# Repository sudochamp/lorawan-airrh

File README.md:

> [!IMPORTANT]
> This project is a work in progress. The board is routed and passes DRC but has not been fabricated or tested yet.

# LoRaWAN AirRH

A slim, battery-powered LoRaWAN sensor node for monitoring temperature and humidity in warehouses, cold storage, greenhouses and FMCG storage. Readings are shown on an e-ink display, logged to onboard flash and sent to a LoRaWAN gateway. It runs on two AAA cells and needs no app, Wi-Fi or cloud account.

This repository holds **SKU A (Environmental)**. A mains-powered air-quality variant (SKU B) is planned as a separate board. See [PLAN.md](PLAN.md).

*Top: RAK811 LoRa module, nPM2100 PMIC, sensors, e-ink FPC connector and display booster.*

*Bottom: 2×AAA holder, Tag-Connect SWD pads, and the thermally isolated SHT45 island (top right in the top view).*

## Features

| | |
|---|---|
| **Radio** | LoRaWAN (OTAA) via RAK811 module (STM32L1 + SX1276), EU868, U.FL antenna connector |
| **Temperature / humidity** | Sensirion SHT45 on a slotted, copper-free island to keep board heat off the sensor |
| **Light** | TI OPT3004, 23-bit ambient light with threshold interrupt (door-open / light-exposure logging) |
| **Motion** | ST LIS2DW12, ultra-low-power accelerometer for shock and tilt detection |
| **Display** | 2.13" GDEY0213B74 e-ink panel. It is bistable, so it keeps showing the last reading with no power |
| **Logging** | Winbond W25Q16JV, 16 Mbit SPI flash |
| **Power** | 2×AAA alkaline into a Nordic nPM2100 boost PMIC (0.7–3.4 V input), with a ship/wake button |
| **Debug** | Tag-Connect TC2030 SWD (no header), UART test points |
| **Enclosure target** | IP54 |
| **Operating range** | 0 to +50 °C. The limit comes from the e-ink panel; all other parts are rated to −40 °C |

## Hardware

| Ref | Part | Function |
|---|---|---|
| U2 | RAK811-HF-EU868 | LoRaWAN module and application MCU |
| U3 | nPM2100-QEAA | Boost PMIC, battery fuel gauge, ship mode |
| U1 | SHT45-AD1B | Temperature and humidity |
| U6 | OPT3004DTSR | Ambient light |
| U5 | LIS2DW12TR | Accelerometer |
| U4 | W25Q16JVSS | Data-logging flash |
| J2 | Hirose FH12-24S-0.5SH | 24-pin FPC connector for the e-ink panel |
| J4 | Hirose U.FL-R-SMT-1 | Antenna connector |
| BT1 | Keystone 2468 | 2×AAA battery holder |
| J3 | Tag-Connect TC2030-IDC-NL | SWD programming |

**Buses**
- **I2C1**: SHT45 (0x44), OPT3004 (0x45), LIS2DW12 (0x19), nPM2100, with 4.7 k pull-ups.
- **SPI**: bit-banged SCK/MOSI shared between the display and flash, with separate chip selects. The RAK811 has no free hardware SPI.

## PCB

- 36 × 75.2 mm, 4 layers, 1.6 mm, ENIG, built to JLCPCB standard 4-layer rules (JLC04161H-7628).
- Stackup is signal / GND / GND / signal. Power is routed as traces, and both inner layers are solid ground.
- 50 Ω grounded coplanar waveguide from the RAK811 to the U.FL: 0.371 mm track with a 0.2 mm gap over In1 GND, fenced with ground vias. A pi-match footprint is included (fitted as 0 Ω, capacitors not populated).
- Hexagonal GND stitching-via grid across the board.
- Custom design rules are in [`lorawan-airrh.kicad_dru`](lorawan-airrh/lorawan-airrh.kicad_dru): JLC via and drill limits, the RF track, and clearance for the ±20 V display rails.

## Firmware notes

The board depends on firmware for these:

1. **Raise the supply before the first LoRa transmission.** VSET is left open, so the nPM2100 starts at 3.0 V. The RAK811 needs 3.15–3.45 V, so write `BOOST.VOUT` = 3.3 V over I2C first.
2. **Enable the MCU's internal pull-up on `LIGHT_INT`.** The OPT3004 interrupt output is open-drain and has no external pull-up.
3. **Skip display refreshes below 0 °C** (use the SHT45 reading). The panel is only rated to refresh from 0 to +50 °C, and the last image stays visible anyway.
4. Keep the LIS2DW12 CS and SA0 pins high. They are tied high on the board; driving either low draws about 160 µA through the internal pull-ups.

## Repository layout

```
lorawan-airrh/          KiCad 10 project (schematic, PCB, local symbols/footprints/3D models)
Datasheets/             Datasheets for the main parts
images/                 Board renders
Abstract.md             Product concept and market notes
Design Requirements.md  Requirements for this model
PLAN.md                 Engineering plan, design decisions and status log
```

## Status

- [x] Schematic, ERC clean
- [x] Placement and routing, DRC clean, no schematic mismatches
- [ ] BOM with MPN / LCSC part numbers
- [ ] Confirm the e-ink FPC contact side against a panel sample
- [ ] Fabrication outputs (Gerbers, drill, pick-and-place)
- [ ] Bring-up and firmware

## License

[GPL-3.0](LICENSE)

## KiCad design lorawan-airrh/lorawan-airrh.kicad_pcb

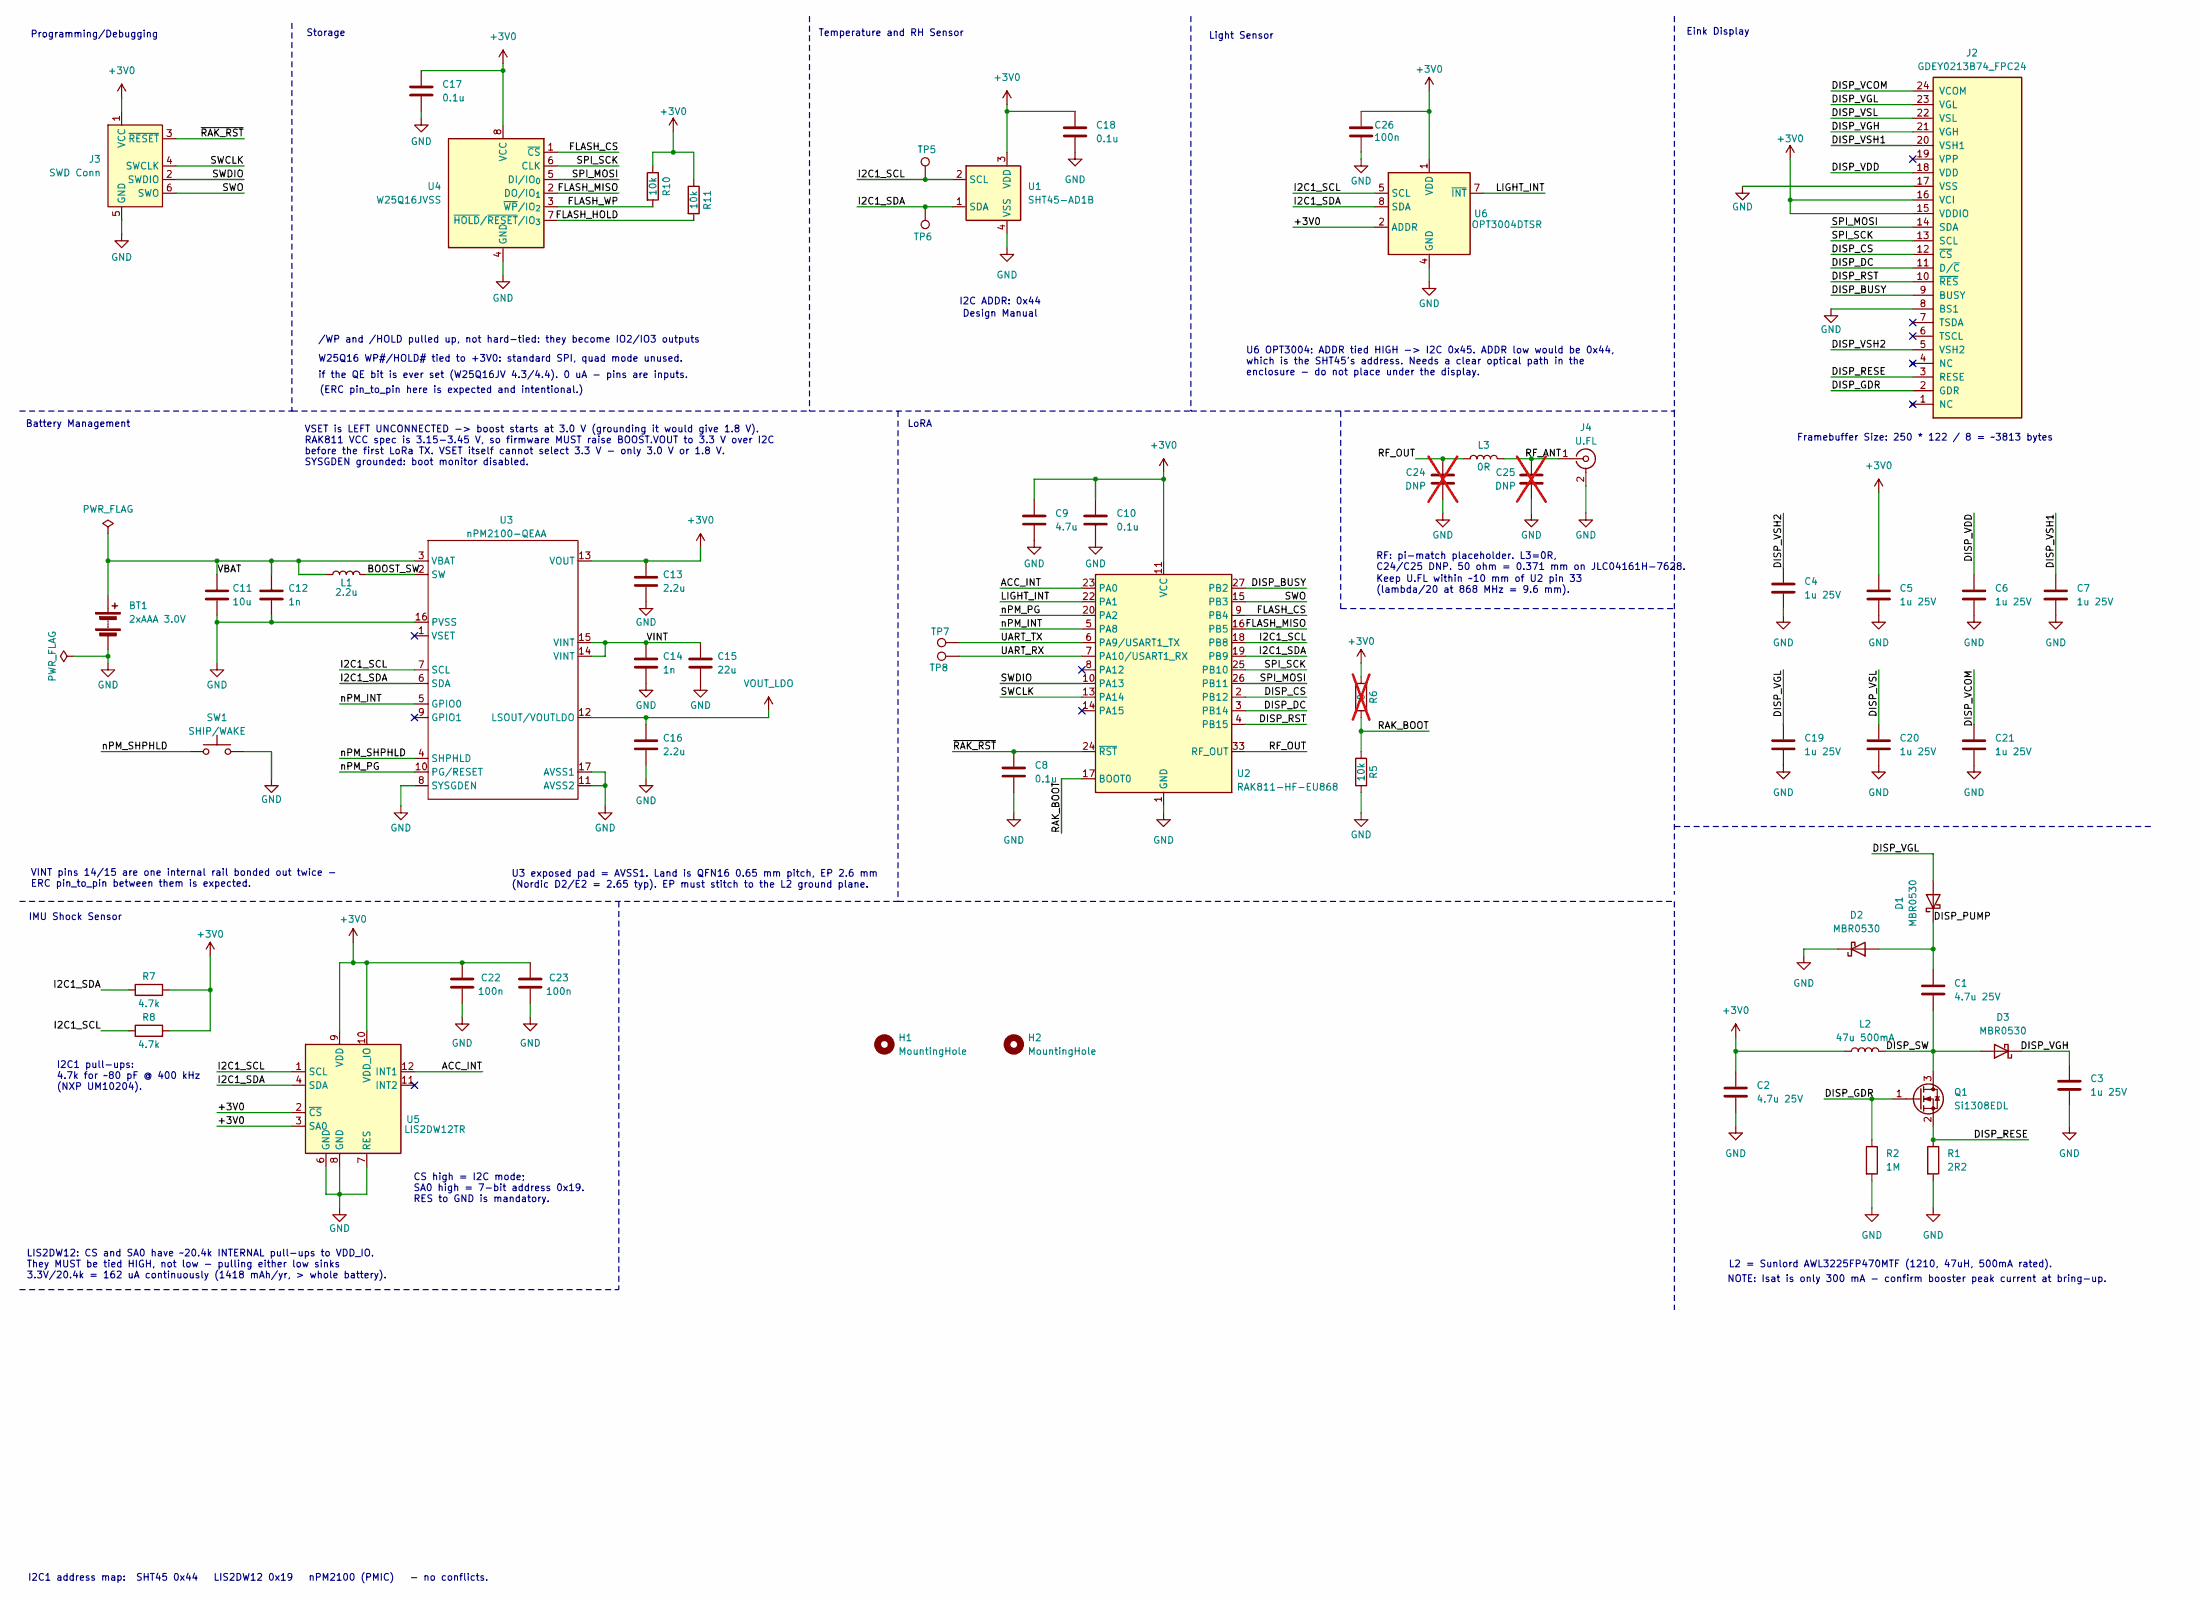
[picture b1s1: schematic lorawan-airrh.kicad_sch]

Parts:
BT1: 2xAAA 3.0V; BatteryHolder_Keystone_2468_2xAAA
C1, C2: 4.7u 25V; C_0805_2012Metric
C3, C4, C5, C6, C7, C19, C20, C21: 1u 25V; C_0603_1608Metric
C8, C10, C17, C18: 0.1u; C_0402_1005Metric
C9: 4.7u; C_0402_1005Metric
C11: 10u; C_0402_1005Metric
C12, C14: 1n; C_0402_1005Metric
C13, C16: 2.2u; C_0402_1005Metric
C15: 22u; C_0402_1005Metric
C22, C23, C26: 100n; C_0402_1005Metric
C24, C25: DNP; C_0402_1005Metric; not fitted
D1, D2, D3: MBR0530; D_SOD-123
H1, H2: MountingHole; MountingHole_2.2mm_M2
J2: GDEY0213B74_FPC24; Hirose_FH12-24S-0.5SH_1x24-1MP_P0.50mm_Horizontal; MPN FH12-24S-0.5SH(55); LCSC C202112
J3: SWD Conn; Tag-Connect_TC2030-IDC-NL_2x03_P1.27mm_Vertical
J4: U.FL; U.FL_Hirose_U.FL-R-SMT-1_Vertical
L1: 2.2u; L_0603_1608Metric
L2: 47u 500mA; L_1210_3225Metric
L3: 0R; L_0402_1005Metric
Q1: Si1308EDL; SOT-323_SC-70
R1: 2R2; R_0603_1608Metric
R2: 1M; R_0402_1005Metric
R5, R10, R11: 10k; R_0402_1005Metric
R6: 0; R_0402_1005Metric; not fitted
R7, R8: 4.7k; R_0402_1005Metric
SW1: SHIP/WAKE; SW_Push_1P1T_XKB_TS-1187A
TP5, TP6, TP7, TP8: TestPoint; TestPoint_Pad_D1.5mm
U1: SHT45-AD1B; Sensirion_DFN-4_1.5x1.5mm_P0.8mm_SHT4x_NoCentralPad
U2: RAK811-HF-EU868; RAK811
U3: nPM2100-QEAA; UQFN-16-1EP_4x4mm_P0.65mm_EP2.6x2.6mm_ThermalVias
U4: W25Q16JVSS; SOIC-8_5.3x5.3mm_P1.27mm
U5: LIS2DW12TR; LGA-12_2x2mm_P0.5mm
U6: OPT3004DTSR; Texas_DTS0008A_SOT-5X3-8_2.1x1.9mm_P0.5mm

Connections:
+3V0: C2.1, C5.1, C9.1, C10.1, C13.1, C17.1, C18.1, C22.1, C23.1, C26.1, J2.15 (VDDIO), J2.16 (VCI), J3.1 (VCC), L2.1, R6.1, R7.2, R8.2, R10.1, R11.1, U1.3 (VDD), U2.11 (VCC), U3.13 (VOUT), U4.8 (VCC), U5.2 (~CS), U5.3 (SA0), U5.9 (VDD), U5.10 (VDD_IO), U6.1 (VDD), U6.2 (ADDR)
/ACC_INT: U2.23 (PA0), U5.12 (INT1)
/BOOST_SW: L1.2, U3.2 (SW)
/DISP_BUSY: J2.9 (BUSY), U2.27 (PB2)
/DISP_CS: J2.12 (~CS), U2.2 (PB12)
/DISP_DC: J2.11 (D/~C), U2.3 (PB14)
/DISP_GDR: J2.2 (GDR), Q1.1 (G), R2.1
/DISP_PUMP: C1.1, D1.1 (K), D2.2 (A)
/DISP_RESE: J2.3 (RESE), Q1.2 (S), R1.1
/DISP_RST: J2.10 (~RES), U2.4 (PB15)
/DISP_SW: C1.2, D3.2 (A), L2.2, Q1.3 (D)
/DISP_VCOM: C21.1, J2.24 (VCOM)
/DISP_VDD: C6.1, J2.18 (VDD)
/DISP_VGH: C3.1, D3.1 (K), J2.21 (VGH)
/DISP_VGL: C19.1, D1.2 (A), J2.23 (VGL)
/DISP_VSH1: C7.1, J2.20 (VSH1)
/DISP_VSH2: C4.1, J2.5 (VSH2)
/DISP_VSL: C20.1, J2.22 (VSL)
/FLASH_CS: U2.9 (PB4), U4.1 (~CS)
/FLASH_HOLD: R11.2, U4.7 (~HOLD/~RESET/IO_{3})
/FLASH_MISO: U2.16 (PB5), U4.2 (DO/IO_{1})
/FLASH_WP: R10.2, U4.3 (~WP/IO_{2})
/I2C1_SCL: R8.1, TP5.1 (1_1), U1.2 (SCL), U2.18 (PB8), U3.7 (SCL), U5.1 (SCL), U6.5 (SCL)
/I2C1_SDA: R7.1, TP6.1 (1_1), U1.1 (SDA), U2.19 (PB9), U3.6 (SDA), U5.4 (SDA), U6.8 (SDA)
/LIGHT_INT: U2.22 (PA1), U6.7 (~INT)
/RAK_BOOT: R5.1, R6.2, U2.17 (BOOT0)
/RF_ANT: C25.1, J4.1 (In), L3.2
/RF_OUT: C24.1, L3.1, U2.33 (RF_OUT)
/SPI_MOSI: J2.14 (SDA), U2.26 (PB11), U4.5 (DI/IO_{0})
/SPI_SCK: J2.13 (SCL), U2.25 (PB10), U4.6 (CLK)
/SWCLK: J3.4 (SWCLK), U2.13 (PA14)
/SWDIO: J3.2 (SWDIO), U2.10 (PA13)
/SWO: J3.6 (SWO), U2.15 (PB3)
/UART_RX: TP8.1 (1_1), U2.7 (PA10/USART1_RX)
/UART_TX: TP7.1 (1_1), U2.6 (PA9/USART1_TX)
/VBAT: BT1.1 (+), C11.1, C12.1, L1.1, U3.3 (VBAT)
/VINT: C14.1, C15.1, U3.14 (VINT), U3.15 (VINT)
/nPM_INT: U2.5 (PA8), U3.5 (GPIO0)
/nPM_PG: U2.20 (PA2), U3.10 (PG/RESET)
/nPM_SHPHLD: SW1.1, U3.4 (SHPHLD)
/~RAK_RST: C8.1, J3.3 (~RESET), U2.24 (~RST)
GND: BT1.2 (-), C2.2, C3.2, C4.2, C5.2, C6.2, C7.2, C8.2, C9.2, C10.2, C11.2, C12.2, C13.2, C14.2, C15.2, C16.2, C17.2, C18.2, C19.2, C20.2, C21.2, C22.2, C23.2, C24.2, C25.2, C26.2, D2.1 (K), J2.8 (BS1), J2.17 (VSS), J3.5 (GND), J4.2 (Ext), R1.2, R2.2, R5.2, SW1.2, U1.4 (VSS), U2.1 (GND), U2.12 (GND), U2.21 (GND), U2.28 (GND), U2.29 (GND), U2.30 (GND), U2.31 (GND), U2.32 (GND), U2.34 (GND), U3.8 (SYSGDEN), U3.11 (AVSS2), U3.16 (PVSS), U3.17 (AVSS1), U4.4 (GND), U5.6 (GND), U5.7 (RES), U5.8 (GND), U6.4 (GND)
VOUT_LDO: C16.1, U3.12 (LSOUT/VOUTLDO)

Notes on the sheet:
U3 exposed pad = AVSS1. Land is QFN16 0.65 mm pitch, EP 2.6 mm (Nordic D2/E2 = 2.65 typ). EP must stitch to the L2 ground plane.
Keep U.FL within ~10 mm of U2 pin 33 (lambda/20 at 868 MHz = 9.6 mm).
I2C1 pull-ups: 4.7k for ~80 pF @ 400 kHz (NXP UM10204).
Design Manual
Battery Management
VINT pins 14/15 are one internal rail bonded out twice - ERC pin_to_pin between them is expected.
RF: pi-match placeholder. L3=0R, C24/C25 DNP. 50 ohm = 0.371 mm on JLC04161H-7628.
Eink Display
/WP and /HOLD pulled up, not hard-tied: they become IO2/IO3 outputs
IMU Shock Sensor
Programming/Debugging
(ERC pin_to_pin here is expected and intentional.)
I2C1 address map: SHT45 0x44 LIS2DW12 0x19 nPM2100 (PMIC) - no conflicts.
CS high = I2C mode; SA0 high = 7-bit address 0x19. RES to GND is mandatory.
if the QE bit is ever set (W25Q16JV 4.3/4.4). 0 uA - pins are inputs.
Temperature and RH Sensor
LoRA
L2 = Sunlord AWL3225FP470MTF (1210, 47uH, 500mA rated).
Light Sensor
VSET is LEFT UNCONNECTED -> boost starts at 3.0 V (grounding it would give 1.8 V). RAK811 VCC spec is 3.15-3.45 V, so firmware MUST raise BOOST.VOUT to 3.3 V over I2C before the first LoRa TX. VSET itself cannot select 3.3 V - only 3.0 V or 1.8 V. SYSGDEN grounded: boot monitor disabled.
NOTE: Isat is only 300 mA - confirm booster peak current at bring-up.
I2C ADDR: 0x44
U6 OPT3004: ADDR tied HIGH -> I2C 0x45. ADDR low would be 0x44, which is the SHT45's address. Needs a clear optical path in the enclosure - do not place under the display.
Framebuffer Size: 250 * 122 / 8 = ~3813 bytes
Storage
W25Q16 WP#/HOLD# tied to +3V0: standard SPI, quad mode unused.
LIS2DW12: CS and SA0 have ~20.4k INTERNAL pull-ups to VDD_IO. They MUST be tied HIGH, not low - pulling either low sinks 3.3V/20.4k = 162 uA continuously (1418 mAh/yr, > whole battery).

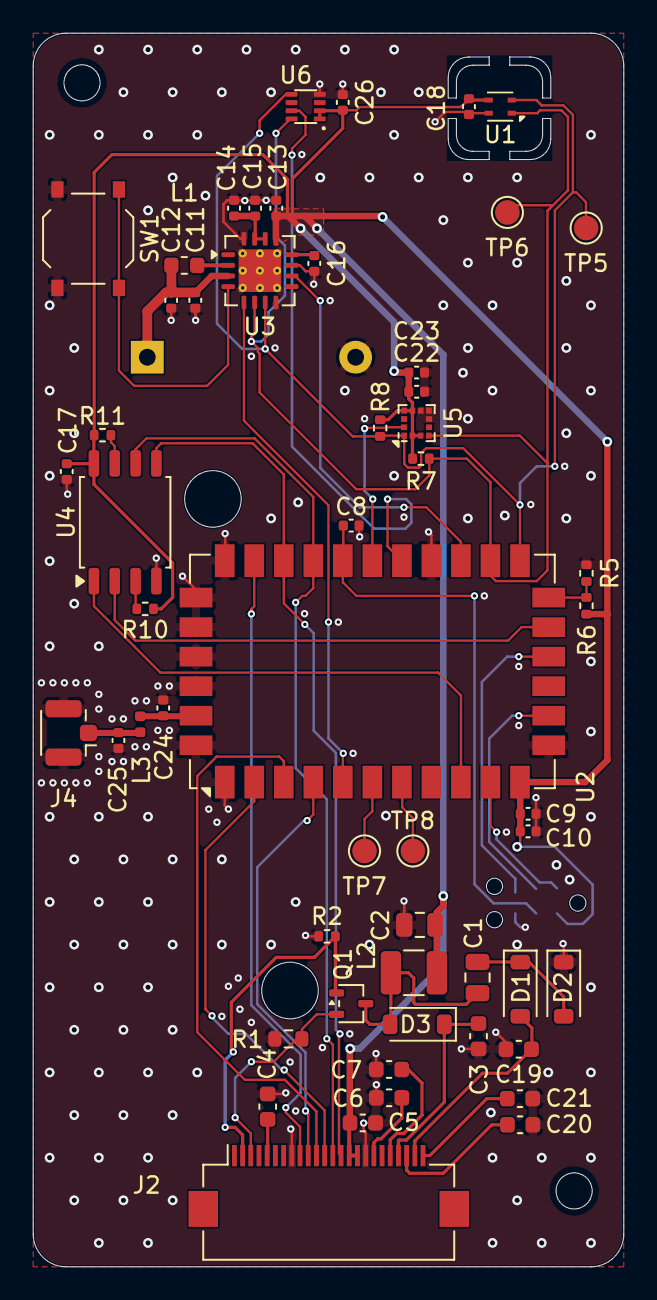
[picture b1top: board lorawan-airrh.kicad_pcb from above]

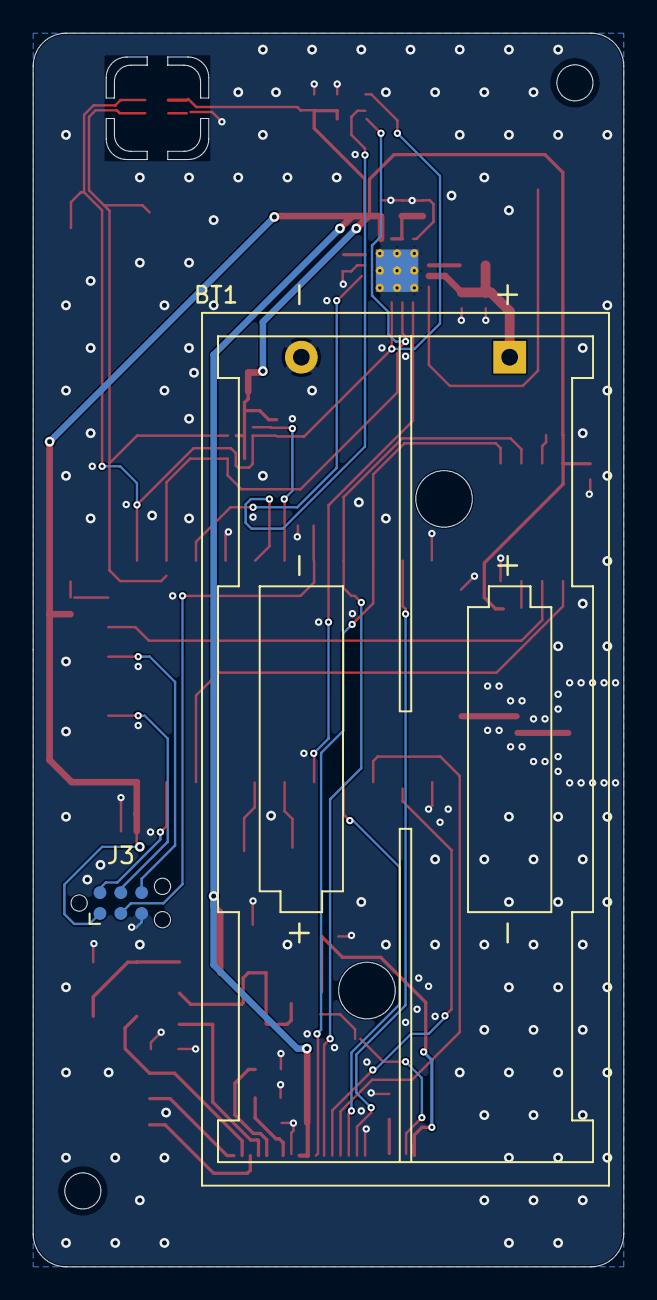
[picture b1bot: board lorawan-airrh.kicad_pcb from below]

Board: 4 copper layers, 36.0 x 75.2 mm, 58 parts (2 on the bottom side), 43 nets.

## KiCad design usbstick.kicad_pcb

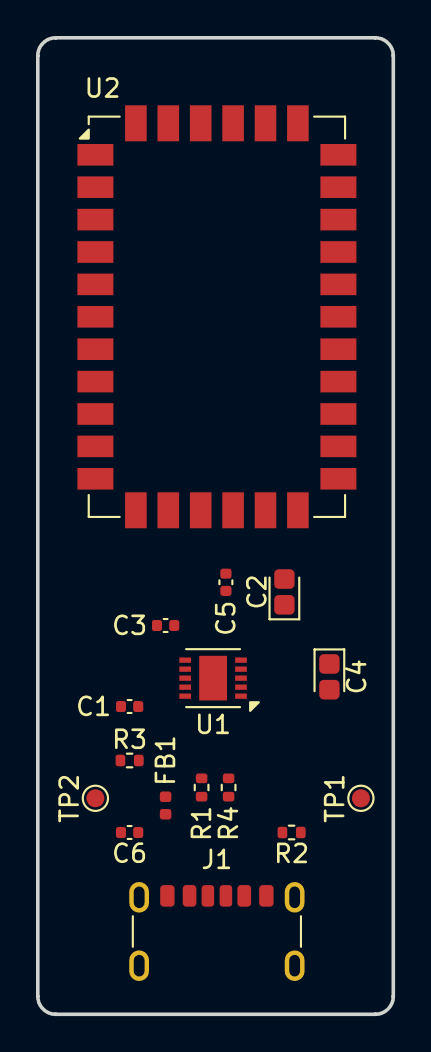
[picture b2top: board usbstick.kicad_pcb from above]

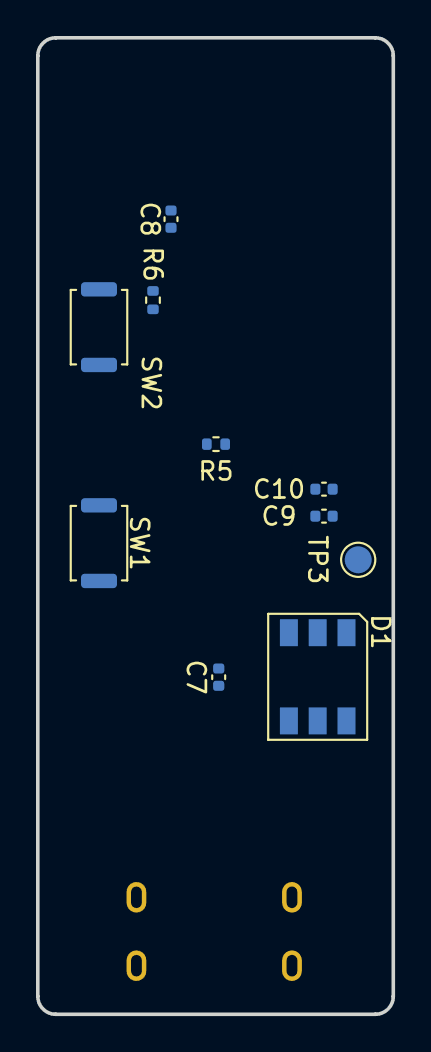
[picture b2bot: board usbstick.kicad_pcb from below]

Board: 2 copper layers, 19.8 x 54.2 mm, 26 parts (10 on the bottom side), 16 nets, no tracks yet.

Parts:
C1, C3, C5, C7, C8, C10: 0.1u; C_0402_1005Metric
C2, C4: 4.7u; CP_EIA-1608-08_AVX-J
C6: 10nF; C_0402_1005Metric
C9: 4.7u; C_0402_1005Metric
D1: WS2812; LED_WS2812_PLCC6_5.0x5.0mm_P1.6mm
FB1: FerriteBead; L_0402_1005Metric
J1: USB_C_Receptacle_USB2.0_14P; USB_C_Receptacle_GCT_USB4125-xx-x_6P_TopMnt_Horizontal
R1, R4: 27; R_0402_1005Metric
R2, R3: 5.1k; R_0402_1005Metric
R5, R6: 10k; R_0402_1005Metric
SW1, SW2: SW_Push; SW_Push_SPST_NO_Alps_SKRK
TP1, TP2: TestPoint; TestPoint_Pad_D1.0mm
TP3: TestPoint; TestPoint_Pad_D1.5mm
U1: FT200XD; DFN-10-1EP_3x3mm_P0.5mm_EP1.55x2.48mm
U2: RAK811-HF-EU868; RAK811

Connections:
+3V3: C3.1, C4.1, C5.1, C7.1, C9.1, C10.1, D1.3 (VCC), D1.5 (VDD), R6.1, SW1.2, U1.3 (3V3OUT), U1.7 (VCCIO), U2.11 (VCC)
+5V: C1.1, C2.1, FB1.2, U1.4 (VCC)
GND: C1.2, C2.2, C3.2, C4.2, C5.2, C6.2, C7.2, C8.2, C9.2, C10.2, D1.6 (VSS), J1.A12 (GND), J1.B12 (GND), J1.S1 (SHIELD), R2.1, R3.1, R5.2, SW2.1, U1.2 (~RESET), U1.9 (GND), U1.11 (GND), U2.1 (GND), U2.12 (GND), U2.21 (GND), U2.28 (GND), U2.29 (GND), U2.30 (GND), U2.31 (GND), U2.32 (GND), U2.34 (GND)
I2C1_SCL: U1.6 (SCL), U2.18 (PB8)
I2C1_SDA: U1.8 (SDA), U2.19 (PB9)
LED_IN: D1.2 (DIN), U2.13 (PA14)
unnamed: D1.1 (DOUT), TP3.1
unnamed: J1.A5 (CC1), R3.2
unnamed: J1.B5 (CC2), R2.2
unnamed: R4.1, TP1.1
unnamed: R1.1, TP2.1
RAK_BOOT: R5.1, SW1.1, U2.17 (BOOT0)
USBD+: R4.2, U1.10 (USBDP)
USBD-: R1.2, U1.1 (USBDM)
VBUS: C6.1, FB1.1, J1.A9 (VBUS), J1.B9 (VBUS)
~RST: C8.1, R6.2, SW2.2, U2.24 (~RST)

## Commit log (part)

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2025-10-17 add license and readme
2025-10-17 organize file structure
2025-10-17 add renders
2025-10-17 Include PCB images in README
    Added images of PCB top and bottom views to README.
